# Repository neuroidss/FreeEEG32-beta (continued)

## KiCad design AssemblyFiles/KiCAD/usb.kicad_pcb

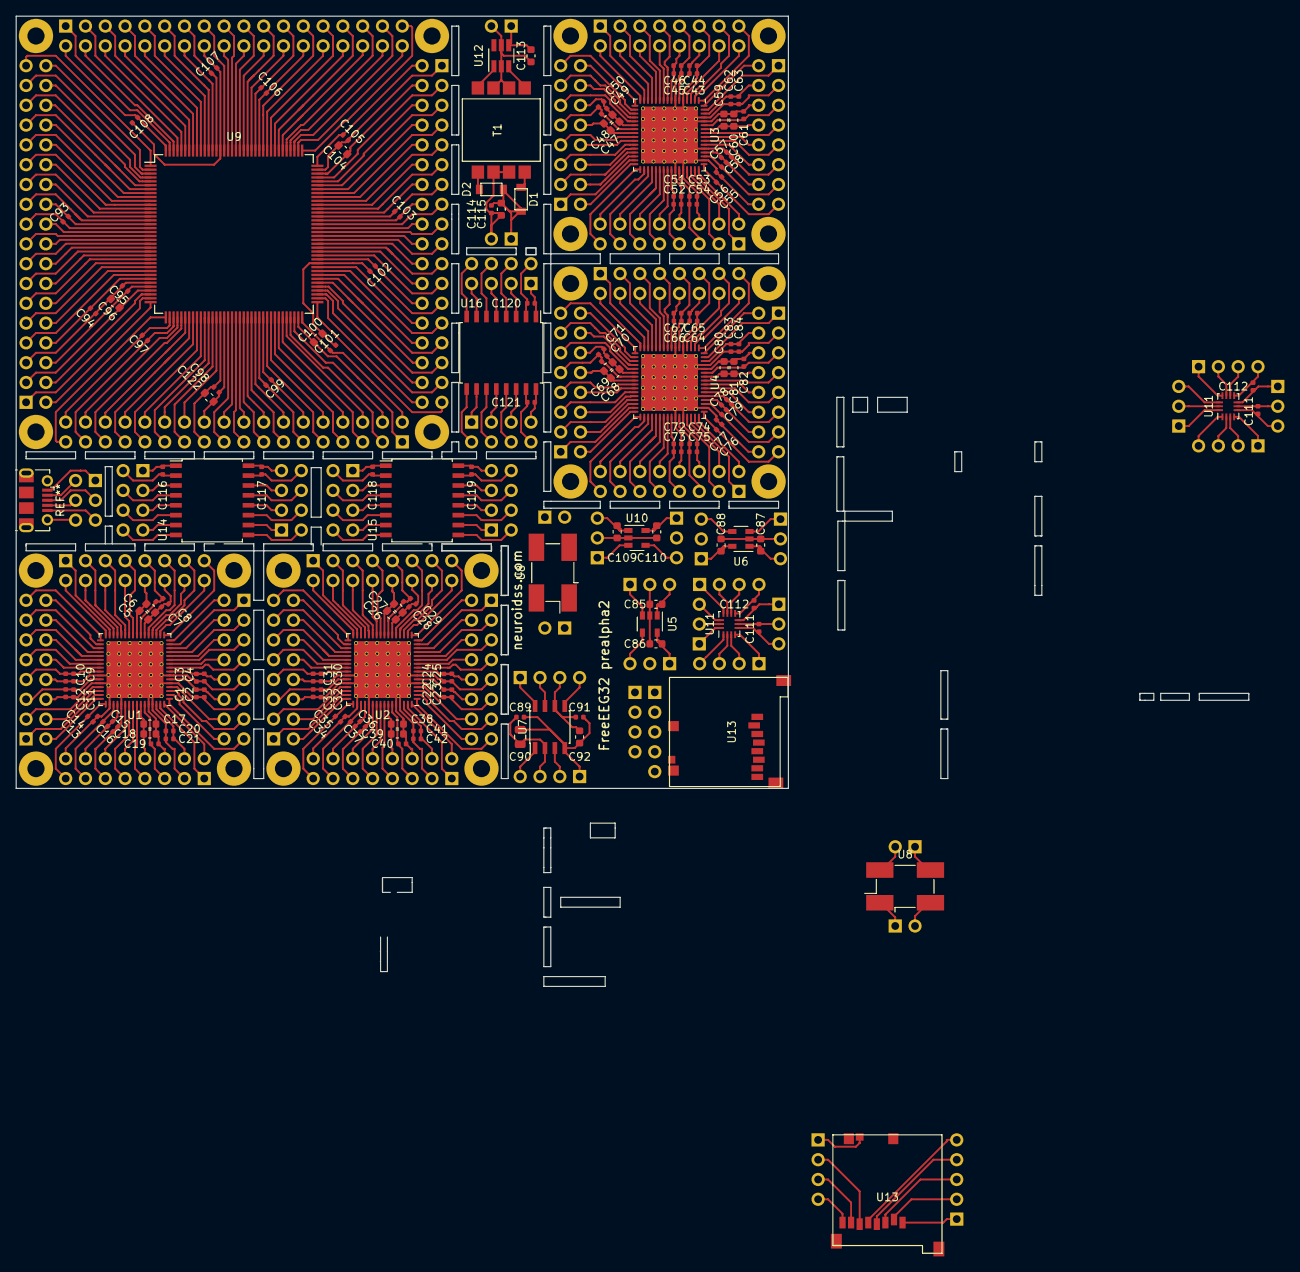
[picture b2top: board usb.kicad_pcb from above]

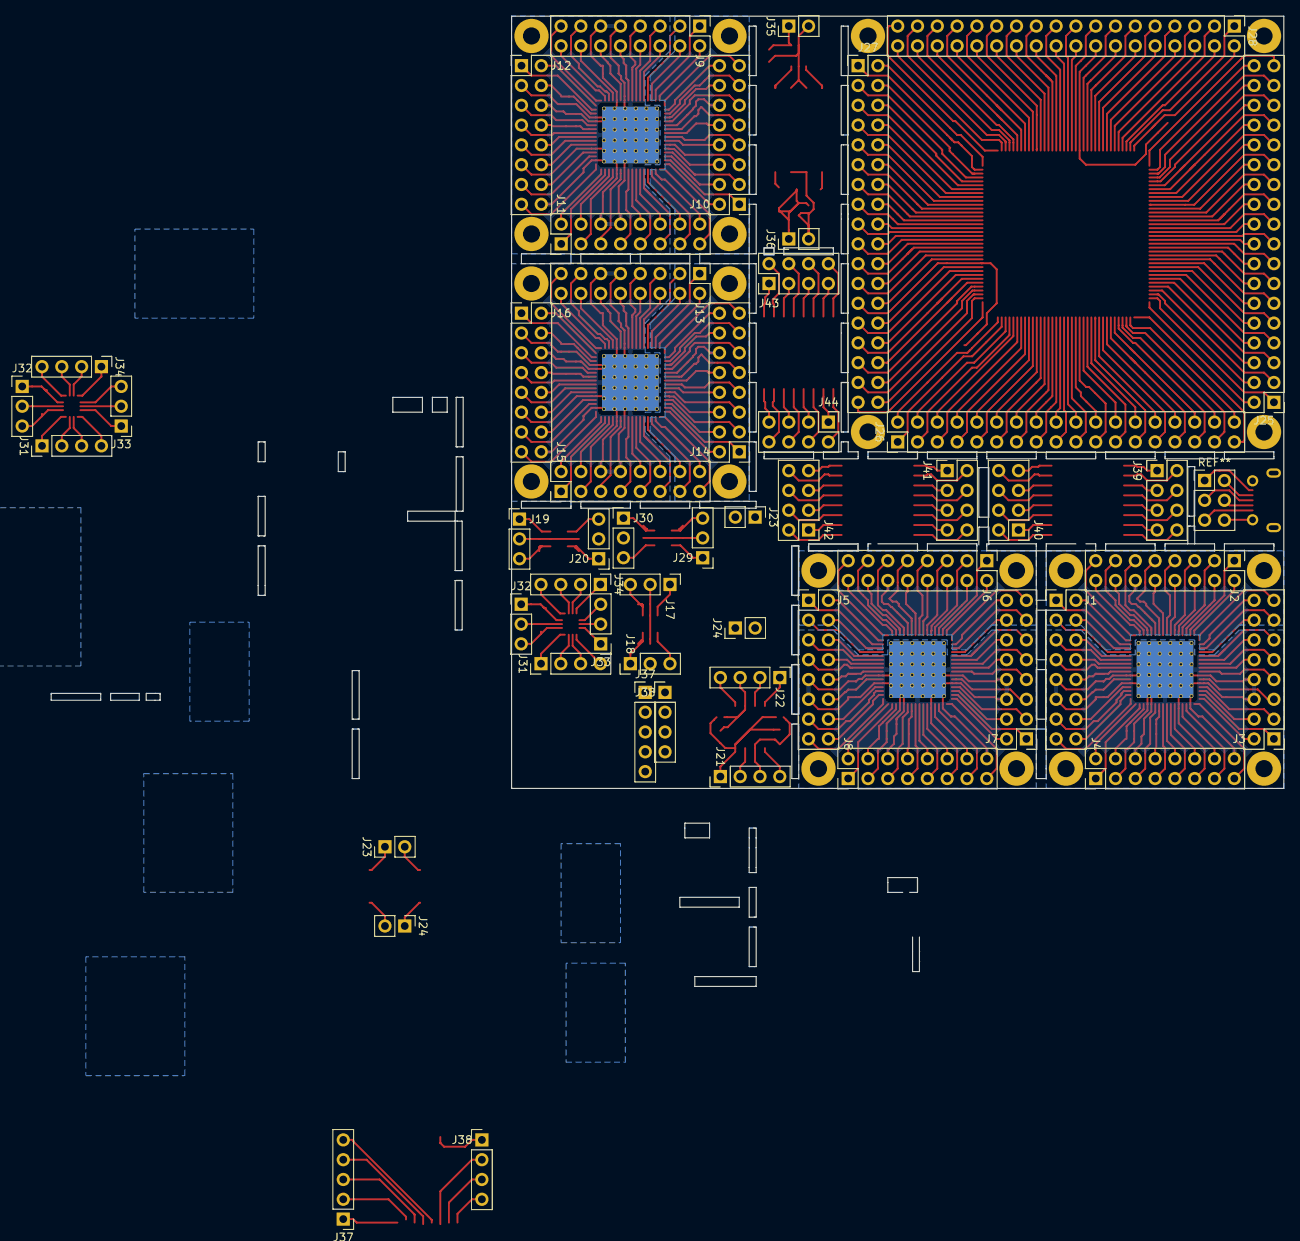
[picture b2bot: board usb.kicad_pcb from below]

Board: 2 copper layers, 99.1 x 99.1 mm, 198 parts (52 on the bottom side), 463 nets.

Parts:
C1, C3, C7, C9, C11, C13, C14, C15, C19, C20, C22, C24, C28, C30, C32, C34, C35, C36, C40, C41, C43, C45, C49, C51, C53, C55, C56, C57, C61, C62, C64, C66, C70, C72, C74, C76, C77, C78, C82, C83, C89, C91, C93, C94, C95, C97, C98, C99, C101, C102, C103, C105, C106, C107, C108, C111, C111#2, C112, C112#2, C114, C116, C117, C118, C119, C120, C121: 100n; C_0402_1005Metric
C2, C4, C8, C10, C12, C16, C21, C23, C25, C29, C31, C33, C37, C42, C44, C46, C50, C52, C54, C58, C63, C65, C67, C71, C73, C75, C79, C84: 1u; C_0402_1005Metric
C5, C17, C26, C38, C47, C59, C68, C80, C96: 100n; C_0603_1608Metric
C6, C18, C27, C39, C48, C60, C69, C81: 1u; C_0603_1608Metric
C85, C86, C87, C88, C100, C104, C109, C110: 2.2u; C_0603_1608Metric
C90: 22u; C_0805_2012Metric
C92, C113, C115: 10u; C_0603_1608Metric
C122: 4.7u; C_0603_1608Metric
D1, D2: D_Schottky; SOD−123
J1, J2, J3, J4, J5, J6, J7, J8, J9, J10, J11, J12, J13, J14, J15, J16: Conn_02x08_Odd_Even; PinHeader_2x08_P2.54mm_Vertical
J17, J18, J19, J20, J29, J30, J32, J32#2, J33, J33#2: Conn_01x03; PinHeader_1x03_P2.54mm_Vertical
J21, J22, J31, J31#2, J34, J34#2, J38, J38#2: Conn_01x04; PinHeader_1x04_P2.54mm_Vertical
J23, J23#2, J24, J24#2, J35, J36: Conn_01x02; PinHeader_1x02_P2.54mm_Vertical
J25, J26, J27, J28: Conn_02x18_Odd_Even; PinHeader_2x18_P2.54mm_Vertical
J37, J37#2: Conn_01x05; PinHeader_1x05_P2.54mm_Vertical
J39, J40, J41, J42, J43, J44: Conn_02x04_Odd_Even; PinHeader_2x04_P2.54mm_Vertical
T1: da2303; SMT Power Transformer
U1, U2, U3, U4: AD7779; QFN-64-1EP_9x9mm_P0.5mm_EP7.3x7.3mm_ThermalVias
U5, U6, U10: LP5907; SOT-23-5
U7: ADR4525; SOIC-8_3.9x4.9mm_P1.27mm
U8, U8#2: FXO-SM7_OSC-SMD7050_short; Oscillator_SMD_EuroQuartz_XO91-4Pin_7.0x5.0mm_HandSoldering
U9: STM32F765ZITx; LQFP-144_20x20mm_P0.5mm
U11, U11#2: LSM6DS3; Bosch_LGA-14_3x2.5mm_P0.5mm
U12: SN6505A; SOT-23-6_Handsoldering
U13, U13#2: 473521001
U14, U15, U16: ISO7341c; SOIC-16W_7.5x10.3mm_P1.27mm

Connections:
/ACCEL&GYRO/1: J31.4, J31#2.4, U11.1, U11#2.1
/ACCEL&GYRO/2: J31.3, J31#2.3, U11.2, U11#2.2
/ACCEL&GYRO/3: J31.2, J31#2.2, U11.3, U11#2.3
/ACCEL&GYRO/4: J31.1, J31#2.1, U11.4, U11#2.4
/ACCEL&GYRO/5: C111.1, C111#2.1, J32.3, J32#2.3, U11.5, U11#2.5
/ACCEL&GYRO/6: C111.2, C111#2.2, J32.2, J32#2.2, U11.6, U11#2.6
/ACCEL&GYRO/7: C112.2, C112#2.2, J32.1, J32#2.1, U11.7, U11#2.7
/ACCEL&GYRO/8: C112.1, C112#2.1, J34.4, J34#2.4, U11.8, U11#2.8
/ACCEL&GYRO/9: J34.3, J34#2.3, U11.9, U11#2.9
/ACCEL&GYRO/10: J34.2, J34#2.2, U11.10, U11#2.10
/ACCEL&GYRO/11: J34.1, J34#2.1, U11.11, U11#2.11
/ACCEL&GYRO/12: J33.3, J33#2.3, U11.12, U11#2.12
/ACCEL&GYRO/13: J33.2, J33#2.2, U11.13, U11#2.13
/ACCEL&GYRO/14: J33.1, J33#2.1, U11.14, U11#2.14
/ADC1/1: J1.15, U1.1
/ADC1/2: J1.16, U1.2
/ADC1/3: J1.13, U1.3
/ADC1/4: J1.14, U1.4
/ADC1/6: C1.2, C2.2, J1.12, U1.6
/ADC1/8: C3.2, C4.2, J1.10, U1.8
/ADC1/9: J1.7, U1.9
/ADC1/10: J1.8, U1.10
/ADC1/11: J1.5, U1.11
/ADC1/12: J1.6, U1.12
/ADC1/13: J1.3, U1.13
/ADC1/14: J1.4, U1.14
/ADC1/15: J1.1, U1.15
/ADC1/16: J1.2, U1.16
/ADC1/17: J2.15, U1.17
/ADC1/18: J2.16, U1.18
/ADC1/19: J2.13, U1.19
/ADC1/20: J2.14, U1.20
/ADC1/21: J2.11, U1.21
/ADC1/23: C7.2, C8.2, J2.9, U1.23
/ADC1/24: C5.2, C6.2, J2.10, U1.24
/ADC1/25: J2.7, U1.25
/ADC1/26: J2.8, U1.26
/ADC1/27: J2.5, U1.27
/ADC1/28: J2.6, U1.28
/ADC1/29: J2.3, U1.29
/ADC1/30: J2.4, U1.30
/ADC1/31: J2.1, U1.31
/ADC1/32: J2.2, U1.32
/ADC1/33: J3.15, U1.33
/ADC1/34: J3.16, U1.34
/ADC1/35: J3.13, U1.35
/ADC1/36: J3.14, U1.36
/ADC1/37: J3.11, U1.37
/ADC1/38: J3.12, U1.38
/ADC1/39: J3.9, U1.39
/ADC1/40: J3.10, U1.40
/ADC1/41: C9.2, C10.2, J3.7, U1.41
/ADC1/43: C11.2, C12.2, J3.5, U1.43
/ADC1/45: J3.3, U1.45
/ADC1/46: J3.4, U1.46
/ADC1/47: J3.1, U1.47
/ADC1/48: J3.2, U1.48
/ADC1/49: C13.1, J4.15, U1.49
/ADC1/51: C14.1, J4.13, U1.51
/ADC1/52: C15.2, C16.2, J4.14, U1.52
/ADC1/54: J4.12, U1.54
/ADC1/55: J4.9, U1.55
/ADC1/56: J4.10, U1.56
/ADC1/57: J4.7, U1.57
/ADC1/58: C17.2, C18.2, J4.8, U1.58
/ADC1/59: C19.1, J4.5, U1.59
/ADC1/62: C20.1, C21.1, J4.4, U1.62
/ADC1/63: J4.1, U1.63
/ADC1/64: J4.2, U1.64
/ADC2/1: J5.15, U2.1
/ADC2/2: J5.16, U2.2
/ADC2/3: J5.13, U2.3
/ADC2/4: J5.14, U2.4
/ADC2/6: C22.2, C23.2, J5.12, U2.6
/ADC2/8: C24.2, C25.2, J5.10, U2.8
/ADC2/9: J5.7, U2.9
/ADC2/10: J5.8, U2.10
/ADC2/11: J5.5, U2.11
/ADC2/12: J5.6, U2.12
/ADC2/13: J5.3, U2.13
/ADC2/14: J5.4, U2.14
/ADC2/15: J5.1, U2.15
/ADC2/16: J5.2, U2.16
/ADC2/17: J6.15, U2.17
/ADC2/18: J6.16, U2.18
/ADC2/19: J6.13, U2.19
/ADC2/20: J6.14, U2.20
/ADC2/21: J6.11, U2.21
/ADC2/23: C28.2, C29.2, J6.9, U2.23
/ADC2/24: C26.2, C27.2, J6.10, U2.24
/ADC2/25: J6.7, U2.25
/ADC2/26: J6.8, U2.26
/ADC2/27: J6.5, U2.27
/ADC2/28: J6.6, U2.28
/ADC2/29: J6.3, U2.29
/ADC2/30: J6.4, U2.30
/ADC2/31: J6.1, U2.31
/ADC2/32: J6.2, U2.32
/ADC2/33: J7.15, U2.33
/ADC2/34: J7.16, U2.34
/ADC2/35: J7.13, U2.35
/ADC2/36: J7.14, U2.36
/ADC2/37: J7.11, U2.37
/ADC2/38: J7.12, U2.38
/ADC2/39: J7.9, U2.39
/ADC2/40: J7.10, U2.40
/ADC2/41: C30.2, C31.2, J7.7, U2.41
/ADC2/43: C32.2, C33.2, J7.5, U2.43
/ADC2/45: J7.3, U2.45
/ADC2/46: J7.4, U2.46
/ADC2/47: J7.1, U2.47
/ADC2/48: J7.2, U2.48
/ADC2/49: C34.1, J8.15, U2.49
/ADC2/51: C35.1, J8.13, U2.51
/ADC2/52: C36.2, C37.2, J8.14, U2.52
/ADC2/54: J8.12, U2.54
/ADC2/55: J8.9, U2.55
/ADC2/56: J8.10, U2.56
/ADC2/57: J8.7, U2.57
/ADC2/58: C38.2, C39.2, J8.8, U2.58
/ADC2/59: C40.1, J8.5, U2.59
/ADC2/62: C41.1, C42.1, J8.4, U2.62
/ADC2/63: J8.1, U2.63
/ADC2/64: J8.2, U2.64
/ADC3/1: J9.15, U3.1
/ADC3/2: J9.16, U3.2
/ADC3/3: J9.13, U3.3
/ADC3/4: J9.14, U3.4
/ADC3/6: C43.2, C44.2, J9.12, U3.6
/ADC3/8: C45.2, C46.2, J9.10, U3.8
/ADC3/9: J9.7, U3.9
/ADC3/10: J9.8, U3.10
/ADC3/11: J9.5, U3.11
/ADC3/12: J9.6, U3.12
/ADC3/13: J9.3, U3.13
/ADC3/14: J9.4, U3.14
/ADC3/15: J9.1, U3.15
/ADC3/16: J9.2, U3.16
/ADC3/17: J10.15, U3.17
/ADC3/18: J10.16, U3.18
/ADC3/19: J10.13, U3.19
/ADC3/20: J10.14, U3.20
/ADC3/21: J10.11, U3.21
/ADC3/23: C49.2, C50.2, J10.9, U3.23
/ADC3/24: C47.2, C48.2, J10.10, U3.24
/ADC3/25: J10.7, U3.25
/ADC3/26: J10.8, U3.26
/ADC3/27: J10.5, U3.27
/ADC3/28: J10.6, U3.28
/ADC3/29: J10.3, U3.29
/ADC3/30: J10.4, U3.30
/ADC3/31: J10.1, U3.31
/ADC3/32: J10.2, U3.32
/ADC3/33: J11.15, U3.33
/ADC3/34: J11.16, U3.34
/ADC3/35: J11.13, U3.35
/ADC3/36: J11.14, U3.36
/ADC3/37: J11.11, U3.37
/ADC3/38: J11.12, U3.38
/ADC3/39: J11.9, U3.39
/ADC3/40: J11.10, U3.40
/ADC3/41: C51.2, C52.2, J11.7, U3.41
/ADC3/43: C53.2, C54.2, J11.5, U3.43
/ADC3/45: J11.3, U3.45
/ADC3/46: J11.4, U3.46
/ADC3/47: J11.1, U3.47
/ADC3/48: J11.2, U3.48
/ADC3/49: C55.1, J12.15, U3.49
/ADC3/51: C56.1, J12.13, U3.51
/ADC3/52: C57.2, C58.2, J12.14, U3.52
/ADC3/54: J12.12, U3.54
/ADC3/55: J12.9, U3.55
/ADC3/56: J12.10, U3.56
/ADC3/57: J12.7, U3.57
/ADC3/58: C59.2, C60.2, J12.8, U3.58
/ADC3/59: C61.1, J12.5, U3.59
/ADC3/62: C62.1, C63.1, J12.4, U3.62
/ADC3/63: J12.1, U3.63
/ADC3/64: J12.2, U3.64
/ADC4/1: J13.15, U4.1
/ADC4/2: J13.16, U4.2
/ADC4/3: J13.13, U4.3
/ADC4/4: J13.14, U4.4
/ADC4/6: C64.2, C65.2, J13.12, U4.6
/ADC4/8: C66.2, C67.2, J13.10, U4.8
/ADC4/9: J13.7, U4.9
/ADC4/10: J13.8, U4.10
/ADC4/11: J13.5, U4.11
/ADC4/12: J13.6, U4.12
/ADC4/13: J13.3, U4.13
/ADC4/14: J13.4, U4.14
/ADC4/15: J13.1, U4.15
/ADC4/16: J13.2, U4.16
/ADC4/17: J14.15, U4.17
/ADC4/18: J14.16, U4.18
/ADC4/19: J14.13, U4.19
/ADC4/20: J14.14, U4.20
/ADC4/21: J14.11, U4.21
/ADC4/23: C70.2, C71.2, J14.9, U4.23
/ADC4/24: C68.2, C69.2, J14.10, U4.24
/ADC4/25: J14.7, U4.25
/ADC4/26: J14.8, U4.26
/ADC4/27: J14.5, U4.27
/ADC4/28: J14.6, U4.28
/ADC4/29: J14.3, U4.29
/ADC4/30: J14.4, U4.30
/ADC4/31: J14.1, U4.31
/ADC4/32: J14.2, U4.32
/ADC4/33: J15.15, U4.33
/ADC4/34: J15.16, U4.34
/ADC4/35: J15.13, U4.35
/ADC4/36: J15.14, U4.36
/ADC4/37: J15.11, U4.37
/ADC4/38: J15.12, U4.38
/ADC4/39: J15.9, U4.39
/ADC4/40: J15.10, U4.40
/ADC4/41: C72.2, C73.2, J15.7, U4.41
/ADC4/43: C74.2, C75.2, J15.5, U4.43
/ADC4/45: J15.3, U4.45
/ADC4/46: J15.4, U4.46
/ADC4/47: J15.1, U4.47
/ADC4/48: J15.2, U4.48
/ADC4/49: C76.1, J16.15, U4.49
/ADC4/51: C77.1, J16.13, U4.51
/ADC4/52: C78.2, C79.2, J16.14, U4.52
/ADC4/54: J16.12, U4.54
/ADC4/55: J16.9, U4.55
/ADC4/56: J16.10, U4.56
/ADC4/57: J16.7, U4.57
/ADC4/58: C80.2, C81.2, J16.8, U4.58
/ADC4/59: C82.1, J16.5, U4.59
/ADC4/62: C83.1, C84.1, J16.4, U4.62
/ADC4/63: J16.1, U4.63
/ADC4/64: J16.2, U4.64
/AVDD/1: C109.1, J29.3, U10.1
/AVDD/2: C109.2, C110.2, J29.2, U10.2
/AVDD/3: J29.1, U10.3
/AVDD/4: J30.3, U10.4
/AVDD/5: C110.1, J30.1, U10.5
/CRYSTAL/1: J24.1, J24#2.1, U8.1, U8#2.1
/CRYSTAL/2: J24.2, J24#2.2, U8.2, U8#2.2
/CRYSTAL/3: J23.1, J23#2.1, U8.3, U8#2.3
/CRYSTAL/4: J23.2, J23#2.2, U8.4, U8#2.4
/IOVDD/1: C87.1, J19.3, U6.1
/IOVDD/2: C87.2, C88.2, J19.2, U6.2
/IOVDD/3: J19.1, U6.3
/IOVDD/4: J20.3, U6.4
/IOVDD/5: C88.1, J20.1, U6.5
/ISO1/1: C116.1, J39.1, U14.1
/ISO1/2: C116.2, J39.2, U14.2
/ISO1/3: J39.3, U14.3
/ISO1/4: J39.4, U14.4
/ISO1/5: J39.5, U14.5
/ISO1/6: J39.6, U14.6
/ISO1/7: J39.7, U14.7
/ISO1/8: J39.8, U14.8
/ISO1/9: J40.2, U14.9
/ISO1/10: J40.1, U14.10
/ISO1/11: J40.4, U14.11
/ISO1/12: J40.3, U14.12
/ISO1/13: J40.6, U14.13
/ISO1/14: J40.5, U14.14
/ISO1/15: C117.2, J40.8, U14.15
/ISO1/16: C117.1, J40.7, U14.16
/ISO2/1: C118.1, J41.1, U15.1
/ISO2/2: C118.2, J41.2, U15.2
/ISO2/3: J41.3, U15.3
/ISO2/4: J41.4, U15.4
/ISO2/5: J41.5, U15.5
/ISO2/6: J41.6, U15.6
/ISO2/7: J41.7, U15.7
/ISO2/8: J41.8, U15.8
/ISO2/9: J42.2, U15.9
/ISO2/10: J42.1, U15.10
/ISO2/11: J42.4, U15.11
/ISO2/12: J42.3, U15.12
/ISO2/13: J42.6, U15.13
/ISO2/14: J42.5, U15.14
/ISO2/15: C119.2, J42.8, U15.15
/ISO2/16: C119.1, J42.7, U15.16
/ISO3/1: C120.1, J43.1, U16.1
/ISO3/2: C120.2, J43.2, U16.2
/ISO3/3: J43.3, U16.3
/ISO3/4: J43.4, U16.4
/ISO3/5: J43.5, U16.5
/ISO3/6: J43.6, U16.6
/ISO3/7: J43.7, U16.7
/ISO3/8: J43.8, U16.8
/ISO3/9: J44.2, U16.9
/ISO3/10: J44.1, U16.10
/ISO3/11: J44.4, U16.11
/ISO3/12: J44.3, U16.12
/ISO3/13: J44.6, U16.13
/ISO3/14: J44.5, U16.14
/ISO3/15: C121.2, J44.8, U16.15
/ISO3/16: C121.1, J44.7, U16.16
/MCU/1: J25.35, U9.1
/MCU/2: J25.36, U9.2
/MCU/3: J25.33, U9.3
/MCU/4: J25.34, U9.4
/MCU/5: J25.31, U9.5
/MCU/6: J25.32, U9.6
/MCU/7: J25.29, U9.7
/MCU/8: J25.30, U9.8
/MCU/9: J25.27, U9.9
/MCU/10: J25.28, U9.10
/MCU/11: J25.25, U9.11
/MCU/12: J25.26, U9.12
/MCU/13: J25.23, U9.13
/MCU/14: J25.24, U9.14
/MCU/15: J25.21, U9.15
/MCU/17: C93.1, J25.19, U9.17
/MCU/18: J25.20, U9.18
/MCU/19: J25.17, U9.19
/MCU/20: J25.18, U9.20
/MCU/21: J25.15, U9.21
/MCU/22: J25.16, U9.22
/MCU/23: J25.13, U9.23
/MCU/24: J25.14, U9.24
/MCU/25: J25.11, U9.25
/MCU/26: J25.12, U9.26
/MCU/27: J25.9, U9.27
/MCU/28: J25.10, U9.28
/MCU/29: J25.7, U9.29
/MCU/30: C94.1, J25.8, U9.30
/MCU/32: C95.1, J25.6, U9.32
/MCU/33: C96.1, J25.3, U9.33
/MCU/34: J25.4, U9.34
/MCU/35: J25.1, U9.35
/MCU/36: J25.2, U9.36
/MCU/37: J26.35, U9.37
/MCU/39: C97.1, J26.33, U9.39
/MCU/40: J26.34, U9.40
/MCU/41: J26.31, U9.41
/MCU/42: J26.32, U9.42
/MCU/43: J26.29, U9.43
/MCU/44: J26.30, U9.44
/MCU/45: J26.27, U9.45
/MCU/46: J26.28, U9.46
/MCU/47: J26.25, U9.47
/MCU/48: J26.26, U9.48
/MCU/49: J26.23, U9.49
/MCU/50: J26.24, U9.50
/MCU/52: C98.1, C122.1, J26.22, U9.52
/MCU/53: J26.19, U9.53
/MCU/54: J26.20, U9.54
/MCU/55: J26.17, U9.55
/MCU/56: J26.18, U9.56
/MCU/57: J26.15, U9.57
/MCU/58: J26.16, U9.58
/MCU/59: J26.13, U9.59
/MCU/60: J26.14, U9.60
/MCU/62: C99.1, J26.12, U9.62
/MCU/63: J26.9, U9.63
/MCU/64: J26.10, U9.64
/MCU/65: J26.7, U9.65
/MCU/66: J26.8, U9.66
/MCU/67: J26.5, U9.67
/MCU/68: J26.6, U9.68
/MCU/69: J26.3, U9.69
/MCU/70: J26.4, U9.70
/MCU/71: C100.1, J26.1, U9.71
/MCU/72: C101.1, J26.2, U9.72
/MCU/73: J27.35, U9.73
/MCU/74: J27.36, U9.74
/MCU/75: J27.33, U9.75
/MCU/76: J27.34, U9.76
/MCU/77: J27.31, U9.77
/MCU/78: J27.32, U9.78
/MCU/79: J27.29, U9.79
/MCU/80: J27.30, U9.80
/MCU/81: J27.27, U9.81
/MCU/82: J27.28, U9.82
/MCU/84: C102.1, J27.26, U9.84
/MCU/85: J27.23, U9.85
/MCU/86: J27.24, U9.86
/MCU/87: J27.21, U9.87
/MCU/88: J27.22, U9.88
/MCU/89: J27.19, U9.89
/MCU/90: J27.20, U9.90
/MCU/91: J27.17, U9.91
/MCU/92: J27.18, U9.92
/MCU/93: J27.15, U9.93
/MCU/95: C103.1, J27.13, U9.95
/MCU/96: J27.14, U9.96
/MCU/97: J27.11, U9.97
/MCU/98: J27.12, U9.98
/MCU/99: J27.9, U9.99
/MCU/100: J27.10, U9.100
/MCU/101: J27.7, U9.101
/MCU/102: J27.8, U9.102
/MCU/103: J27.5, U9.103
/MCU/104: J27.6, U9.104
/MCU/105: J27.3, U9.105
/MCU/106: C104.1, J27.4, U9.106
/MCU/108: C105.1, J27.2, U9.108
/MCU/109: J28.35, U9.109
/MCU/110: J28.36, U9.110
/MCU/111: J28.33, U9.111
/MCU/112: J28.34, U9.112
/MCU/113: J28.31, U9.113
/MCU/114: J28.32, U9.114
/MCU/115: J28.29, U9.115
/MCU/116: J28.30, U9.116
/MCU/117: J28.27, U9.117
/MCU/118: J28.28, U9.118
/MCU/119: J28.25, U9.119
/MCU/121: C106.1, J28.23, U9.121
/MCU/122: J28.24, U9.122
/MCU/123: J28.21, U9.123
/MCU/124: J28.22, U9.124
/MCU/125: J28.19, U9.125
/MCU/126: J28.20, U9.126
/MCU/127: J28.17, U9.127
/MCU/128: J28.18, U9.128
/MCU/129: J28.15, U9.129
/MCU/131: C107.1, J28.13, U9.131
/MCU/132: J28.14, U9.132
/MCU/133: J28.11, U9.133
/MCU/134: J28.12, U9.134
/MCU/135: J28.9, U9.135
/MCU/136: J28.10, U9.136
/MCU/137: J28.7, U9.137
/MCU/138: J28.8, U9.138
/MCU/139: J28.5, U9.139
/MCU/140: J28.6, U9.140
/MCU/141: J28.3, U9.141
/MCU/142: J28.4, U9.142
/MCU/143: J28.1, U9.143
/MCU/144: C108.1, J28.2, U9.144
/POWER/1: C113.1, J35.1, U12.4
/POWER/2: C113.2, J35.2, T1.2, T1.3, U12.2, U12.5
/POWER/3: C114.1, C115.1, D1.1, D2.1, J36.1
/POWER/4: C114.2, C115.2, J36.2, T1.6, T1.7
/REF/1: J21.4, U7.1
/REF/2: C89.1, C90.1, J21.3, U7.2
/REF/3: J21.2, U7.3
/REF/4: C89.2, C90.2, C91.2, C92.2, J21.1, U7.4
/REF/5: J22.4, U7.5
/REF/6: C91.1, C92.1, J22.3, U7.6
/REF/7: J22.2, U7.7
/REF/8: J22.1, U7.8
/SD/1: J37.1, J37#2.1, U13.1, U13#2.1
/SD/2: J37.2, J37#2.2, U13.2, U13#2.2
/SD/3: J37.3, J37#2.3, U13.3, U13#2.3
/SD/4: J37.4, J37#2.4, U13.4, U13#2.4
/SD/5: J37.5, J37#2.5, U13.5, U13#2.5
/SD/6: J38.2, J38#2.2, U13.6, U13#2.6
/SD/7: J38.3, J38#2.3, U13.7, U13#2.7
/SD/8: J38.4, J38#2.4, U13.8, U13#2.8
/SD/9: J38.1, J38#2.1, U13.9, U13#2.9
/VDD/1: C85.1, J17.3, U5.1
/VDD/2: C85.2, C86.2, J17.2, U5.2
/VDD/3: J17.1, U5.3
/VDD/4: J18.3, U5.4
/VDD/5: C86.1, J18.1, U5.5
AVSS: C1.1, C2.1, C3.1, C4.1, C9.1, C10.1, C11.1, C12.1, C13.2, C14.2, C15.1, C16.1, C17.1, C18.1, C19.2, C20.2, C21.2, C22.1, C23.1, C24.1, C25.1, C30.1, C31.1, C32.1, C33.1, C34.2, C35.2, C36.1, C37.1, C38.1, C39.1, C40.2, C41.2, C42.2, C43.1, C44.1, C45.1, C46.1, C51.1, C52.1, C53.1, C54.1, C55.2, C56.2, C57.1, C58.1, C59.1, C60.1, C61.2, C62.2, C63.2, C64.1, C65.1, C66.1, C67.1, C72.1, C73.1, C74.1, C75.1, C76.2, C77.2, C78.1, C79.1, C80.1, C81.1, C82.2, C83.2, C84.2, J1.9, J1.11, J3.6, J3.8, J4.3, J4.6, J4.11, J4.16, J5.9, J5.11, J7.6, J7.8, J8.3, J8.6, J8.11, J8.16, J9.9, J9.11, J11.6, J11.8, J12.3, J12.6, J12.11, J12.16, J13.9, J13.11, J15.6, J15.8, J16.3, J16.6, J16.11, J16.16, U1.5, U1.7, U1.42, U1.44, U1.50, U1.53, U1.60, U1.61, U1.65, U2.5, U2.7, U2.42, U2.44, U2.50, U2.53, U2.60, U2.61, U2.65, U3.5, U3.7, U3.42, U3.44, U3.50, U3.53, U3.60, U3.61, U3.65, U4.5, U4.7, U4.42, U4.44, U4.50, U4.53, U4.60, U4.61, U4.65
DGND: C5.1, C6.1, C7.1, C8.1, C26.1, C27.1, C28.1, C29.1, C47.1, C48.1, C49.1, C50.1, C68.1, C69.1, C70.1, C71.1, J2.12, J6.12, J10.12, J14.12, U1.22, U2.22, U3.22, U4.22
unnamed: D1.2, T1.8
unnamed: D2.2, T1.5
unnamed: T1.1, U12.3
unnamed: T1.4, U12.1
VSS: C93.2, C94.2, C95.2, C96.2, C97.2, C98.2, C99.2, C100.2, C101.2, C102.2, C103.2, C104.2, C105.2, C106.2, C107.2, C108.2, C122.2, J25.5, J25.22, J26.11, J26.21, J26.36, J27.1, J27.16, J27.25, J28.16, J28.26, U9.16, U9.31, U9.38, U9.51, U9.61, U9.83, U9.94, U9.107, U9.120, U9.130

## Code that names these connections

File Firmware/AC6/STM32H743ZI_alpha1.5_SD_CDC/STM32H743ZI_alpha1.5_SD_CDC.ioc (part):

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Mcu.Name=STM32H743ZITx
Mcu.Package=LQFP144
Mcu.UserName=STM32H743ZITx
PA0.Signal=SharedStack_PA0
PA0.Stacked=true
PA10.Mode=Asynchronous
PA10.Signal=USART1_RX
PA11.Signal=USART1_CTS
PA12.Signal=USART1_RTS
PA13\ (JTMS/SWDIO).Mode=Serial_Wire
PA13\ (JTMS/SWDIO).Signal=DEBUG_JTMS-SWDIO
PA14\ (JTCK/SWCLK).Mode=Serial_Wire
PA14\ (JTCK/SWCLK).Signal=DEBUG_JTCK-SWCLK
PA15\ (JTDI).Mode=NSS_Signal_Hard_Output
PA15\ (JTDI).Signal=SPI3_NSS
PA2.Mode=SAI_B_AsyncSlave
PA2.Signal=SAI2_SCK_B
PA4.GPIOParameters=GPIO_Label
PA4.GPIO_Label=SPI1_NSS
PA4.Signal=SharedStack_PA4
PA4.Stacked=true
PA5.Mode=Full_Duplex_Master
PA5.Signal=SPI1_SCK
PA6.Mode=Full_Duplex_Master
PA6.Signal=SPI1_MISO
PA7.Mode=Full_Duplex_Master
PA7.Signal=SPI1_MOSI
PA9.Mode=Asynchronous
PA9.Signal=USART1_TX
PB0.GPIOParameters=GPIO_Label
PB0.GPIO_Label=ADC1_DRDY
PB0.Signal=GPXTI0
PB1.GPIOParameters=GPIO_Label
PB1.GPIO_Label=ADC3_RESET
PB1.Signal=GPIO_Output
PB12.GPIOParameters=GPIO_Label
PB12.GPIO_Label=SPI2_NSS
PB12.Signal=SharedStack_PB12
PB12.Stacked=true
PB13.Mode=Full_Duplex_Master
PB13.Signal=SPI2_SCK
PB14.GPIOParameters=GPIO_Speed
PB14.GPIO_Speed=GPIO_SPEED_FREQ_LOW
PB14.Mode=Device_Only_FS
PB14.Signal=USB_OTG_HS_DM
PB15.GPIOParameters=GPIO_Speed
PB15.GPIO_Speed=GPIO_SPEED_FREQ_LOW
PB15.Mode=Device_Only_FS
PB15.Signal=USB_OTG_HS_DP
PB2.GPIOParameters=GPIO_Label
PB2.GPIO_Label=BOOT1
PB2.Signal=GPIO_Input
PB3\ (JTDO/TRACESWO).Mode=Full_Duplex_Master
PB3\ (JTDO/TRACESWO).Signal=SPI3_SCK
PB4\ (NJTRST).Mode=Full_Duplex_Master
PB4\ (NJTRST).Signal=SPI3_MISO
PB5.Mode=Full_Duplex_Master
PB5.Signal=SPI3_MOSI
PB6.Mode=I2C
PB6.Signal=I2C1_SCL
PB7.Mode=I2C
PB7.Signal=I2C1_SDA
PB8.GPIOParameters=GPIO_Label
PB8.GPIO_Label=ACC_INT1
PB8.Signal=GPXTI8
PB9.GPIOParameters=GPIO_Label
PB9.GPIO_Label=ACC_SDO_SAO
PB9.Signal=GPIO_Output
PC1.Mode=SAI_A_AsyncSlave
PC1.Signal=SAI1_SD_A
PC10.Mode=SD_4_bits_Wide_bus
PC10.Signal=SDMMC1_D2
PC11.Mode=SD_4_bits_Wide_bus
PC11.Signal=SDMMC1_D3
PC12.Mode=SD_4_bits_Wide_bus
PC12.Signal=SDMMC1_CK
PC13.GPIOParameters=GPIO_Label
PC13.GPIO_Label=ADC2_DRDY
PC13.Signal=GPXTI13
PC2_C.Mode=Full_Duplex_Master
PC2_C.Signal=SPI2_MISO
PC3_C.Mode=Full_Duplex_Master
PC3_C.Signal=SPI2_MOSI
PC5.GPIOParameters=GPIO_Label
PC5.GPIO_Label=ADC3_START
PC5.Signal=GPIO_Output
PC6.Signal=S_TIM8_CH1
PC7.GPIOParameters=GPIO_Label
PC7.GPIO_Label=SDMMC1_DETECT
PC7.Signal=GPIO_Input
PC8.Mode=SD_4_bits_Wide_bus
PC8.Signal=SDMMC1_D0
PC9.Mode=SD_4_bits_Wide_bus
PC9.Signal=SDMMC1_D1
PD1.Mode=SAI_A_SyncSlave
PD1.Signal=SAI3_SD_A
PD11.Mode=SAI_A_AsyncSlave
PD11.Signal=SAI2_SD_A
PD12.Mode=SAI_A_AsyncSlave
PD12.Signal=SAI2_FS_A
PD13.Mode=SAI_A_AsyncSlave
PD13.Signal=SAI2_SCK_A
PD2.Mode=SD_4_bits_Wide_bus
PD2.Signal=SDMMC1_CMD
PD4.GPIOParameters=GPIO_Label
PD4.GPIO_Label=ADC1_START
PD4.Signal=GPIO_Output
PD5.GPIOParameters=GPIO_Label
PD5.GPIO_Label=ADC1_RESET
PD5.Signal=GPIO_Output
PD6.Mode=SAI_A_SyncSlave
PD6.Signal=SAI4_SD_A
PD9.Mode=SAI_B_SyncSlave
PD9.Signal=SAI3_SD_B
PE1.GPIOParameters=GPIO_Label
PE1.GPIO_Label=ACC_INT2
PE1.Signal=GPXTI1
PE11.Mode=NSS_Signal_Hard_Output
PE11.Signal=SPI4_NSS
PE12.Mode=Full_Duplex_Master
PE12.Signal=SPI4_SCK
PE13.Mode=Full_Duplex_Master
PE13.Signal=SPI4_MISO
PE14.Mode=Full_Duplex_Master
PE14.Signal=SPI4_MOSI
PE3.Mode=SAI_B_SyncSlave
PE3.Signal=SAI4_SD_B
PE4.Mode=SAI_A_AsyncSlave
PE4.Signal=SAI1_FS_A
PE5.Mode=SAI_A_AsyncSlave
PE5.Signal=SAI1_SCK_A
PE7.Signal=S_TIM1_ETR
PE9.Signal=S_TIM1_CH1
PF0.Mode=I2C
PF0.Signal=I2C2_SDA
PF1.Mode=I2C
PF1.Signal=I2C2_SCL
PF10.GPIOParameters=GPIO_Label
PF10.GPIO_Label=ADC3_DRDY
PF10.Signal=GPXTI10
PF4.GPIOParameters=GPIO_Label
PF4.GPIO_Label=ADC2_START
PF4.Signal=GPIO_Output
PF5.GPIOParameters=GPIO_Label
PF5.GPIO_Label=ADC2_RESET
PF5.Signal=GPIO_Output
PF6.Mode=SAI_B_AsyncSlave
PF6.Signal=SAI1_SD_B
PF7.GPIOParameters=PinState,GPIO_Label
PF7.GPIO_Label=ISO_USB_PIN
PF7.PinState=GPIO_PIN_SET
PF7.Signal=GPIO_Output
PF8.Mode=SAI_B_AsyncSlave
PF8.Signal=SAI1_SCK_B
PF9.Mode=SAI_B_AsyncSlave
PF9.Signal=SAI1_FS_B
PG10.Mode=SAI_B_AsyncSlave
PG10.Signal=SAI2_SD_B
PG12.Mode=Full_Duplex_Master
PG12.Signal=SPI6_MISO
PG13.Mode=Full_Duplex_Master
PG13.Signal=SPI6_SCK
PG14.Mode=Full_Duplex_Master
PG14.Signal=SPI6_MOSI
PG2.GPIOParameters=GPIO_Label
PG2.GPIO_Label=ADC4_START
PG2.Signal=GPIO_Output
PG3.GPIOParameters=GPIO_Label
PG3.GPIO_Label=ADC4_RESET
PG3.Signal=GPIO_Output
PG4.GPIOParameters=GPIO_Label
PG4.GPIO_Label=ADC4_DRDY
PG4.Signal=GPXTI4
PG8.Mode=NSS_Signal_Hard_Output
PG8.Signal=SPI6_NSS
PG9.Mode=SAI_B_AsyncSlave
PG9.Signal=SAI2_FS_B
RCC.HSE_VALUE=32000000
RCC.SYSCLKFreq_VALUE=480000000
RCC.SYSCLKSource=RCC_SYSCLKSOURCE_PLLCLK
board=custom

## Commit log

2020-09-22 added guides
2020-12-07 removed redundant file
2020-12-07 correct file
2021-03-25 rollback main firmware
2021-07-11 push 80mhz edits, needs more work.
2021-08-11 windows10 usb
2022-02-11 added docker container instructions, don't bother with AC6
2024-11-19 docker network fix
